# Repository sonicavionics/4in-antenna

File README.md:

# Antenna Module Repository

---

<div align="center">
  <div>

    <p><em>3D Render</em></p>
  </div>
  <br>

  <div>
    <br>
    <p><em>Schematic</em></p>
  </div>
  <br>
  
  <div>
    
    <br>
    <em>Footprint</em>
  </div>
</div>

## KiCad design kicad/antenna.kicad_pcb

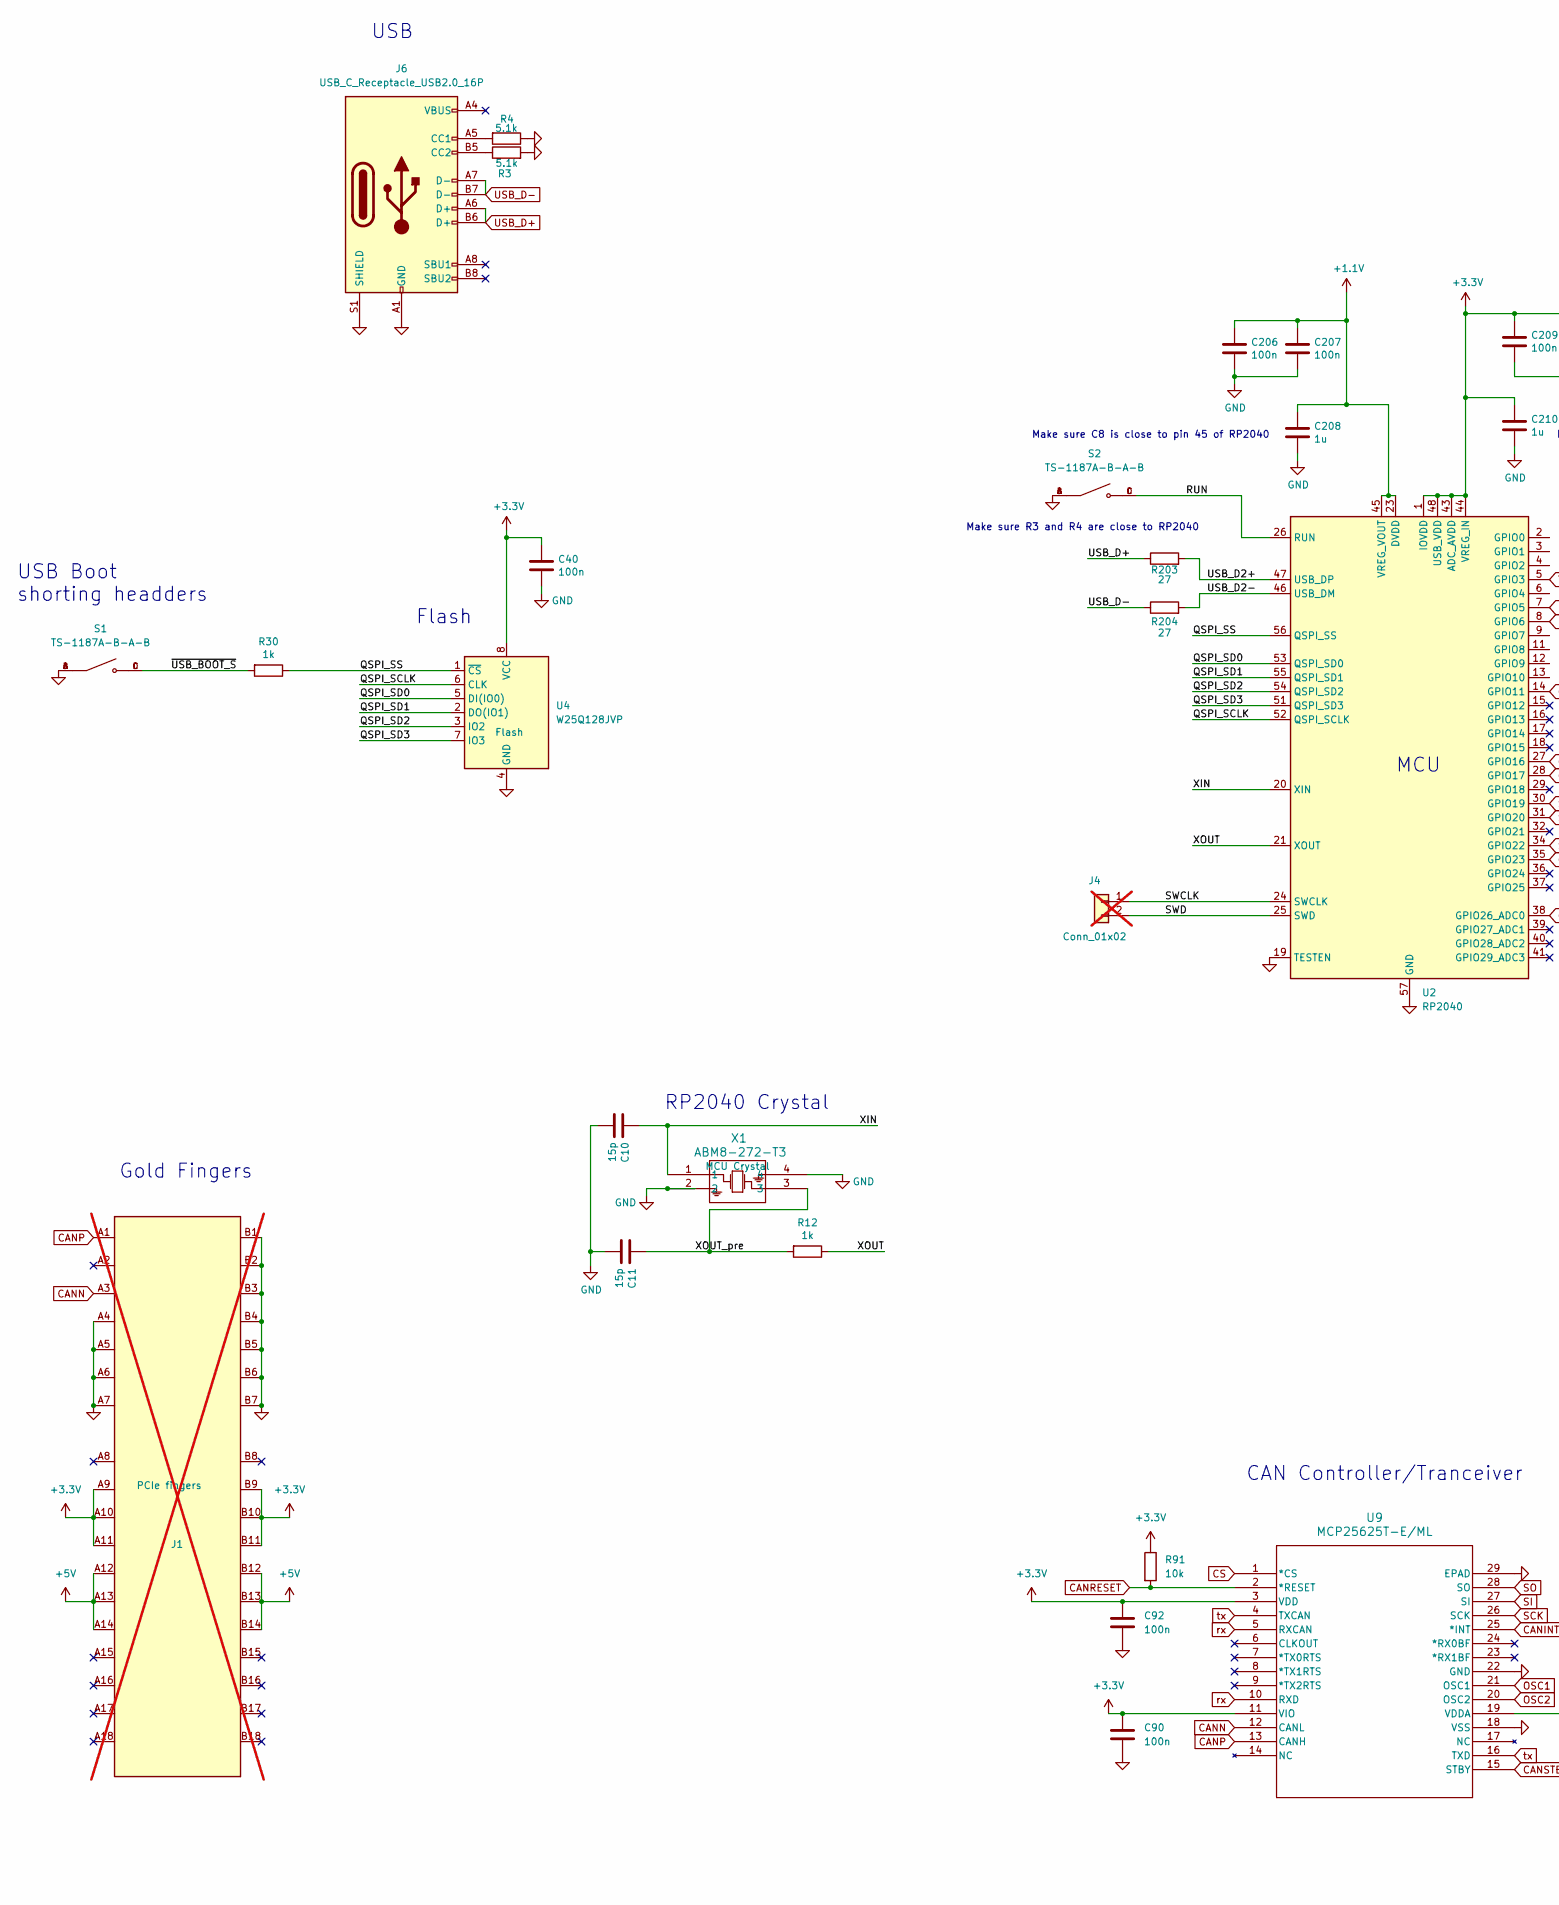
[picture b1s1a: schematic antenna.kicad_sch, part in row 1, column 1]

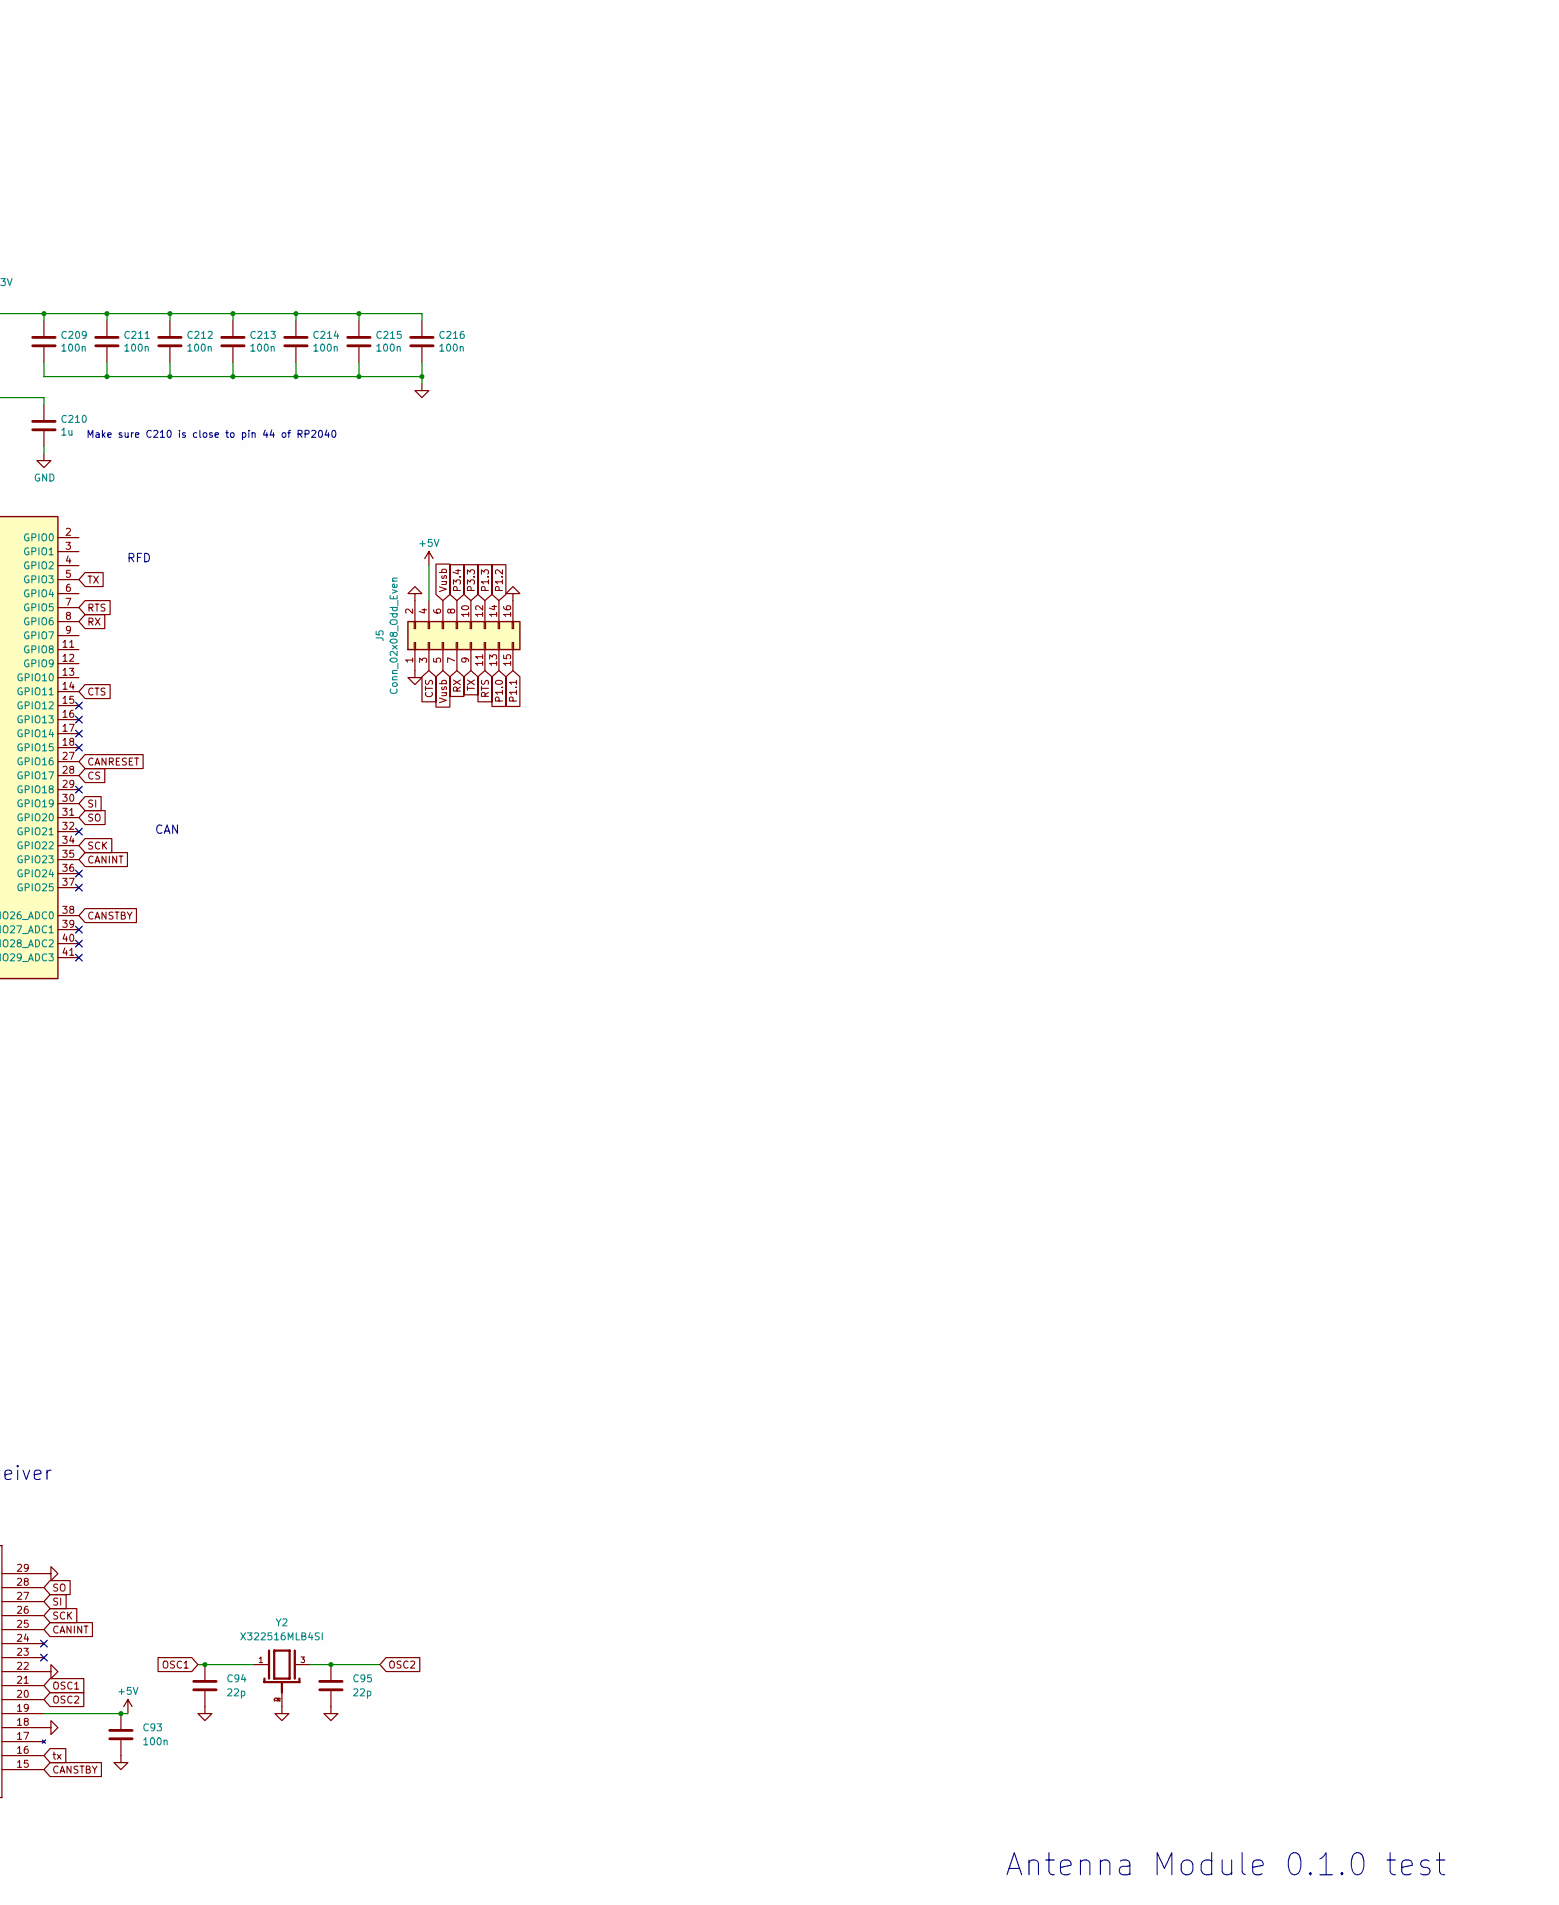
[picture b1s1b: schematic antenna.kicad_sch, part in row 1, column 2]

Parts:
C10, C11: 15p; C_0402_1005Metric; LCSC Part # C1548
C40, C90, C92, C93, C206, C207, C209, C211, C212, C213, C214, C215, C216: 100n; C_0402_1005Metric; LCSC Part # C307331
C94, C95: 22p; C_0402_1005Metric; LCSC Part # C1555
C208, C210: 1u; C_0402_1005Metric; LCSC Part # C52923
J1: Bus_PCI_Express_x1; BUS_PCIexpress_x1; LCSC Part # n/a; not fitted
J4: Conn_01x02; PinHeader_1x02_P2.54mm_Vertical; LCSC Part # n/a; not fitted
J5: Conn_02x08_Odd_Even; PinSocket_2x08_P2.54mm_Vertical
J6: USB_C_Receptacle_USB2.0_16P; USB_C_Receptacle_Palconn_UTC16-G; LCSC Part # C2765186
R3, R4: 5.1k; R_0402_1005Metric; LCSC Part # C25905
R12, R30: 1k; R_0402_1005Metric; LCSC Part # C11702
R91: 10k; R_0402_1005Metric; LCSC Part # C25744
R203, R204: 27; R_0402_1005Metric; LCSC Part # C25100
S1, S2: TS-1187A-B-A-B; SW_TS-1187A-B-A-B; PARTREV A0; LCSC Part # C318884
U2: RP2040; QFN-56-1EP_7x7mm_P0.4mm_EP3.2x3.2mm; LCSC C2040
U4: W25Q128JVP; WSON-8-1EP_6x5mm_P1.27mm_EP3.4x4.3mm; LCSC C190862
U9: MCP25625T-E/ML; QFN28_6X6MC_MCH; LCSC Part # C191253
X1: ABM8-272-T3; ABM8-272-T3_ABR; LCSC Part # C20625731
Y2: X322516MLB4SI; OSC_X322516MLB4SI; PARTREV N/A; LCSC Part # C12668

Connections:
+1.1V: C206.1, C207.1, C208.1, U2.23 (DVDD), U2.45 (VREG_VOUT), U2.50 (DVDD)
+3.3V: C40.1, C90.1, C92.1, C209.1, C210.1, C211.1, C212.1, C213.1, C214.1, C215.1, C216.1, J1.A9 (+3.3V), J1.A10 (+3.3V), J1.A11 (~PERST), J1.B9 (JTAG1), J1.B10 (3.3Vaux), J1.B11 (~WAKE), R91.1, U2.1 (IOVDD), U2.10 (IOVDD), U2.22 (IOVDD), U2.33 (IOVDD), U2.42 (IOVDD), U2.43 (ADC_AVDD), U2.44 (VREG_IN), U2.48 (USB_VDD), U2.49 (IOVDD), U4.8 (VCC), U9.3 (VDD), U9.11 (VIO)
+5V: C93.1, J1.A12 (GND), J1.A13 (REFCLK+), J1.A14 (REFCLK-), J1.B12 (RSVD), J1.B13 (GND), J1.B14 (PETp0), J5.4, U9.19 (VDDA)
/QSPI_SCLK: U2.52 (QSPI_SCLK), U4.6 (CLK)
/QSPI_SD0: U2.53 (QSPI_SD0), U4.5 (DI(IO0))
/QSPI_SD1: U2.55 (QSPI_SD1), U4.2 (DO(IO1))
/QSPI_SD2: U2.54 (QSPI_SD2), U4.3 (IO2)
/QSPI_SD3: U2.51 (QSPI_SD3), U4.7 (IO3)
/QSPI_SS: R30.1, U2.56 (QSPI_SS), U4.1 (~CS)
/RUN: S2.C, S2.D, U2.26 (RUN)
/SWCLK: J4.1, U2.24 (SWCLK)
/SWD: J4.2, U2.25 (SWD)
/USB_D2+: R203.2, U2.47 (USB_DP)
/USB_D2-: R204.2, U2.46 (USB_DM)
/XIN: C10.1, U2.20 (XIN), X1.1
/XOUT: R12.1, U2.21 (XOUT)
/XOUT_pre: C11.1, R12.2, X1.3
/~USB_BOOT_S: R30.2, S1.C, S1.D
CANINT: U2.35 (GPIO23), U9.25 (*INT)
CANN: J1.A3 (+12V), U9.12 (CANL)
CANP: J1.A1 (~PRSNT1), U9.13 (CANH)
CANRESET: R91.2, U2.27 (GPIO16), U9.2 (*RESET)
CANSTBY: U2.38 (GPIO26_ADC0), U9.15 (STBY)
CS: U2.28 (GPIO17), U9.1 (*CS)
CTS: J5.3, U2.14 (GPIO11)
GND: C10.2, C11.2, C40.2, C90.2, C92.2, C93.2, C94.2, C95.2, C206.2, C207.2, C208.2, C209.2, C210.2, C211.2, C212.2, C213.2, C214.2, C215.2, C216.2, J1.A4 (GND), J1.A5 (JTAG2), J1.A6 (JTAG3), J1.A7 (JTAG4), J1.B1 (+12V), J1.B2 (+12V), J1.B3 (+12V), J1.B4 (GND), J1.B5 (SMCLK), J1.B6 (SMDAT), J1.B7 (GND), J5.1, J5.2, J5.16, J6.A1 (GND), J6.A12 (GND), J6.B1 (GND), J6.B12 (GND), J6.S1 (SHIELD), R3.2, R4.1, S1.A, S1.B, S2.A, S2.B, U2.19 (TESTEN), U2.57 (GND), U4.4 (GND), U9.18 (VSS), U9.22 (GND), U9.29 (EPAD), X1.2, X1.4, Y2.2, Y2.4
unnamed: J6.A5 (CC1), R4.2
unnamed: J6.B5 (CC2), R3.1
OSC1: C94.1, U9.21 (OSC1), Y2.1
OSC2: C95.1, U9.20 (OSC2), Y2.3
P1.0: J5.13
P1.1: J5.15
P1.2: J5.14
P1.3: J5.12
P3.3: J5.10
P3.4: J5.8
RTS: J5.11, U2.7 (GPIO5)
RX: J5.7, U2.8 (GPIO6)
SCK: U2.34 (GPIO22), U9.26 (SCK)
SI: U2.30 (GPIO19), U9.27 (SI)
SO: U2.31 (GPIO20), U9.28 (SO)
TX: J5.9, U2.5 (GPIO3)
USB_D+: J6.A6 (D+), J6.B6 (D+), R203.1
USB_D-: J6.A7 (D-), J6.B7 (D-), R204.1
Vusb: J5.5, J5.6
rx: U9.5 (RXCAN), U9.10 (RXD)
tx: U9.4 (TXCAN), U9.16 (TXD)

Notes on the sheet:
Make sure C210 is close to pin 44 of RP2040
Make sure C8 is close to pin 45 of RP2040
RP2040 Crystal
USB
Make sure R3 and R4 are close to RP2040
CAN
RFD
USB Boot shorting headders
Antenna Module 0.1.0 test
Gold Fingers
MCU
CAN Controller/Tranceiver
Flash

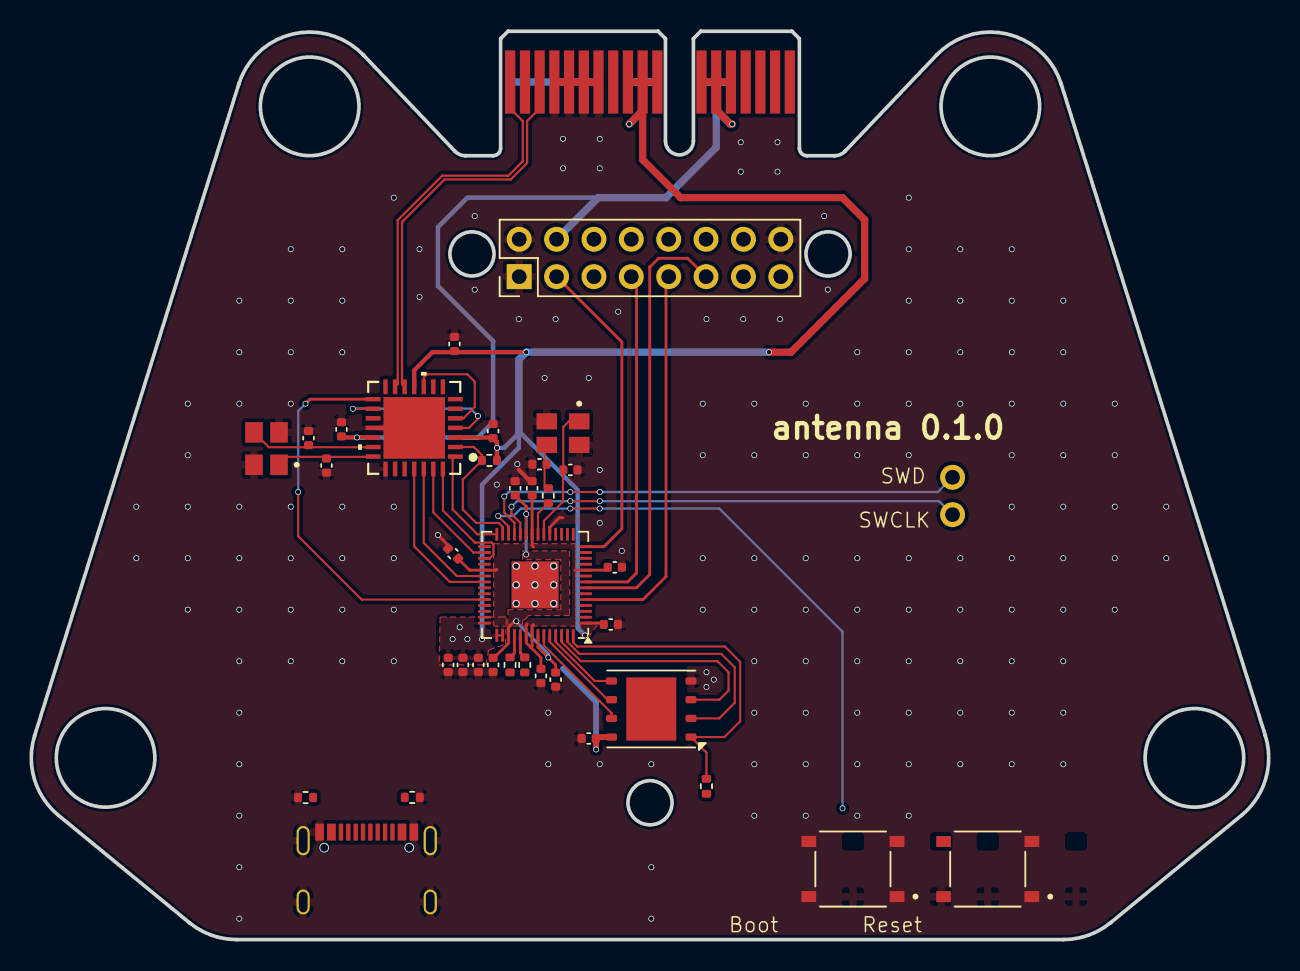
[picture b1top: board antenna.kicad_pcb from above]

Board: 2 copper layers, 84.1 x 61.7 mm, 37 parts (1 on the bottom side), 41 nets.

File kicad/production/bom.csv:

Designator,Footprint,Quantity,Value,LCSC Part #
"C10, C11",0402,2,15p,C1548
"C206, C207, C209, C211, C212, C213, C214, C215, C216, C40, C90, C92, C93",0402,13,100n,C307331
"C208, C210",0402,2,1u,C52923
"C94, C95",0402,2,22p,C1555
J5,PinSocket_2x08_P2.54mm_Vertical,1,Conn_02x08_Odd_Even,
J6,USB_C_Receptacle_Palconn_UTC16-G,1,USB_C_Receptacle_USB2.0_16P,C2765186
"R12, R30",0402,2,1k,C11702
"R203, R204",0402,2,27,C25100
"R3, R4",0402,2,5.1k,C25905
R91,0402,1,10k,C25744
"S1, S2",SW_TS-1187A-B-A-B,2,TS-1187A-B-A-B,C318884
U2,QFN-56-1EP_7x7mm_P0.4mm_EP3.2x3.2mm,1,RP2040,C2040
U4,WSON-8-1EP_6x5mm_P1.27mm_EP3.4x4.3mm,1,W25Q128JVP,C190862
U9,QFN28_6X6MC_MCH,1,MCP25625T-E/ML,C191253
X1,ABM8-272-T3_ABR,1,ABM8-272-T3,C20625731
Y2,OSC_X322516MLB4SI,1,X322516MLB4SI,C12668

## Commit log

2025-01-23 init
2025-01-23 Auto-exported schematic, PCB, and 3D model
2025-01-24 update DXF to new hole positions
2025-01-25 update positioning of all chips to fit rfd900x
2025-01-26 update kicad antenna board
2025-01-26 test
2025-01-26 Append 'test' to test.txt
2025-01-26 Update images
2025-02-11 add MCAD files
2025-02-11 add mcad_exports folder
2025-02-11 reposition usb ports and buttons
